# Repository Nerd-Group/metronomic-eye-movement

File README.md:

# metronomic-eye-movement
driving a WS2812 LED Stripe to move a single dot from one ent to another and back again

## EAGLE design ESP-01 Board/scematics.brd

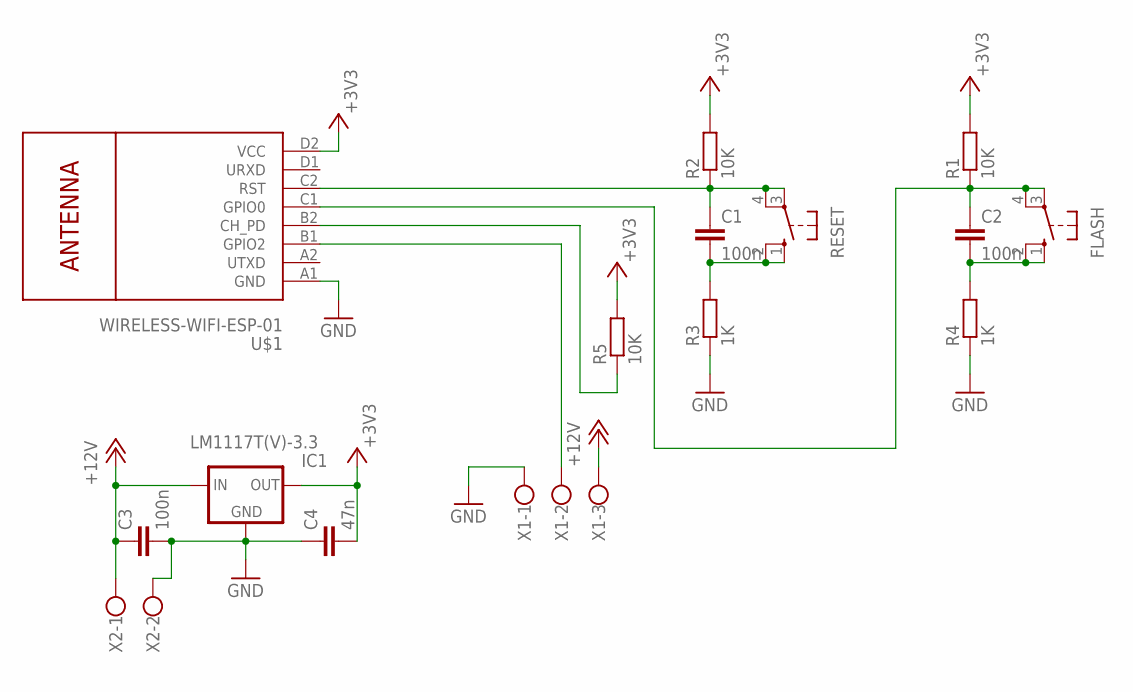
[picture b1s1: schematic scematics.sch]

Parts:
C1, C2, C3: 100n; C050-030X075
C4: 47n; C050-030X075
FLASH: 10-XX; B3F-10XX
IC1: LM1117T(V)-3.3; TO220V
R1, R2, R5: 10K; 0207/10
R3, R4: 1K; 0207/10
RESET: 10-XX; B3F-10XX
U$1: WIRELESS-WIFI-ESP-01
X1: W237-103
X2: W237-102

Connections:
+3V3: C4.2, IC1.2 (OUT), R1.2, R2.2, R5.2, U$1.D2 (VCC)
+12V: C3.1, IC1.3 (IN), X1.3, X2.1
GND: C3.2, C4.1, IC1.1 (GND), R3.1, R4.1, U$1.A1 (GND), X1.1, X2.2
unnamed: C1.1, R2.1, RESET.3, RESET.4 (P1), U$1.C2 (RST)
unnamed: C1.2, R3.2, RESET.1 (S), RESET.2 (S1)
unnamed: C2.1, FLASH.3, FLASH.4 (P1), R1.1, U$1.C1 (GPIO0)
unnamed: C2.2, FLASH.1 (S), FLASH.2 (S1), R4.2
unnamed: R5.1, U$1.B2 (CH_PD)
unnamed: U$1.B1 (GPIO2), X1.2

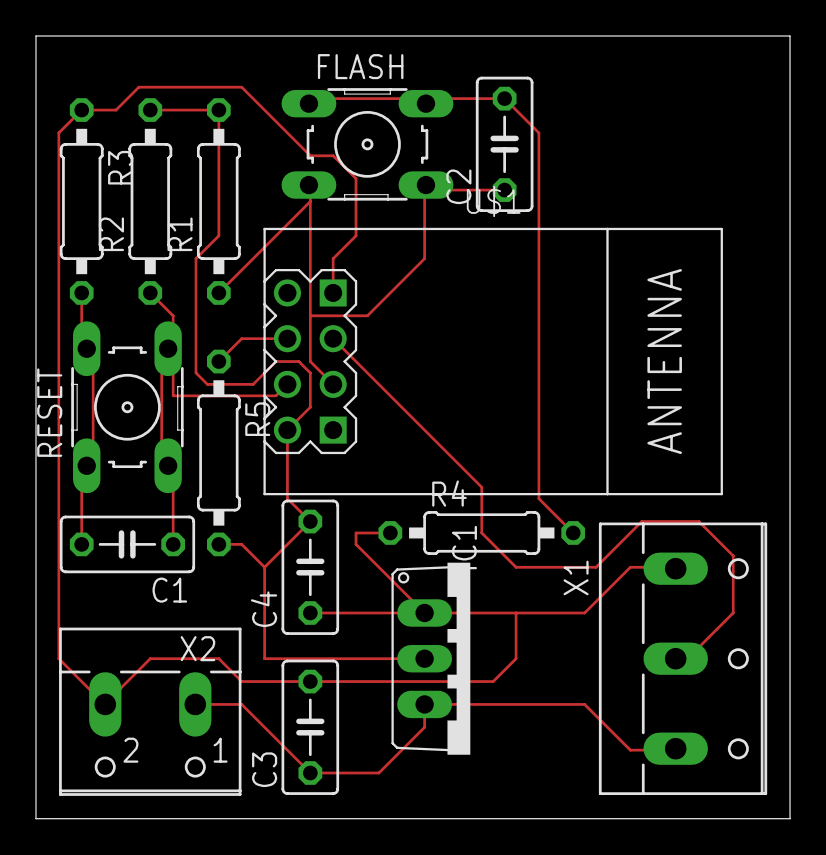
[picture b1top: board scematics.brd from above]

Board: 2 copper layers, 41.9 x 43.5 mm, 15 parts (0 on the bottom side), 9 nets.

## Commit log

2020-10-27 Web interface
    web interface has been implemented. Furthermore ist was put through a minifier for optimisation. Further optimisation, a better layout, tests in other browsers than Firefox and a responsive webdesign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
2020-10-27 started initialising web server on ESP
2020-11-26 WiFi, Web-Server and OTA implementation
2020-11-27 Fixed issue with WiFi Connection
2020-12-08 maybe some bugs are sillt available?
2020-12-10 more debugging statements
2020-12-30 Platine fertig

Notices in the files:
parts and their libraries:
diy-modules: Released under the Creative Commons Attribution 4.0 International License: http://creativecommons.org/licenses/by/4.0
